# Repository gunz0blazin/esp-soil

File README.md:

# esp-soil

> **This is the `testing` branch.** It holds changes that are written but not yet running on the stakes or the dashboard server. `main` matches what's deployed right now. To see exactly what's new here, compare the branches: [`main...testing`](https://github.com/gunz0blazin/esp-soil/compare/main...testing). Once a change is flashed and checked on real hardware, it gets merged into `main` with a pull request.
>
> **In testing now**
> - **Deployment pipeline:** merging to `main` deploys the dashboard to the site's Raspberry Pi automatically (`ansible-pull` on a timer, with phone notifications). Firmware is flashed from the ESPHome add-on in Home Assistant, which pulls the shared firmware from `main`. The stakes are reached from home over Tailscale. Every push and pull request is checked on GitHub first. See [Deployment](#deployment) and [`deploy/README.md`](deploy/README.md).
> - **Shared firmware:** `firmware/common.yaml` is used by every stake; each stake has a small file with its number, IP and calibration (`firmware/stakes/`, plus a template for the Home Assistant add-on).
> - **Encryption:** the Home Assistant connection and every firmware update are encrypted with one key (`api_key`). Stakes no longer reboot when Home Assistant isn't connected.
> - **Board login:** the stake web page and `/metrics` require a username and password. Prometheus logs in using a password file. See [Board login](#board-login-testing).
> - **Dashboard stack:** stakes are listed in `dashboard/prometheus/targets/` (adding one needs no restart), image versions are pinned, the Grafana password comes from `.env`, and the dashboard is now called **Soil Monitor**.

Wi-Fi soil moisture stakes. Each stake is a small board with an ESP32-C3, a capacitive soil probe and an AHT10 temperature/humidity sensor in a 3D printed case. Push it into the soil like a plant marker and plug in a USB cable. It reports soil moisture, temperature, humidity and VPD over Wi-Fi to ESPHome / Home Assistant and Prometheus, and the included Grafana stack graphs it.

> **Status:** the breadboard version works and is graphing in Grafana. The stake PCB and snap-fit case are designed but haven't been built yet. The board is now a full KiCad project (`hardware/kicad/`) with the case in its 3D view. Run ERC/DRC there and plot Gerbers from it before ordering.

<!-- toc -->
**Contents**

- [What's in here](#whats-in-here)
- [The stake](#the-stake)
  - [Parts (per stake)](#parts-per-stake)
  - [Pins](#pins)
  - [Case](#case)
  - [Power](#power)
- [Setup](#setup)
- [Calibrating](#calibrating)
  - [Keeping readings honest](#keeping-readings-honest)
- [Data logging: Prometheus + Grafana](#data-logging-prometheus--grafana)
  - [What's in dashboard/](#whats-in-dashboard)
  - [Quick start](#quick-start)
  - [What a stake sends](#what-a-stake-sends)
  - [Prometheus](#prometheus)
  - [Grafana](#grafana)
  - [Viewing on a phone or remotely](#viewing-on-a-phone-or-remotely)
  - [Board login (testing)](#board-login-testing)
  - [Security notes](#security-notes)
  - [Maintenance](#maintenance)
  - [Troubleshooting](#troubleshooting)
- [Deployment](#deployment)
- [VPD](#vpd)
- [Testing on a breadboard](#testing-on-a-breadboard)
- [License](#license)
<!-- /toc -->

---

## What's in here

```
firmware/
  common.yaml              the stake firmware, shared by every stake
  stakes/                  one small file per stake: number, IP, calibration
  ha-stub.example.yaml     template for a stake in the Home Assistant ESPHome add-on
  moisture-test.yaml       breadboard test board: probe + AHT10 + OLED
  moisture-test-probe-only.yaml   same board, probe + OLED only
  legacy/                  the original 4-probe OLED + touch button build
hardware/
  kicad/                   KiCad project: schematic, PCB, 3D models + the case for fit checks
  pcb/                     v1 hand-made Gerbers, build guide PDF
  case/                    snap-fit case (3MF), OpenSCAD file, print notes
  legacy/                  case for the old 4-probe box
dashboard/                 Prometheus + Grafana in Docker, with the dashboard (see Data logging below)
deploy/                    automatic deploy to the site's Raspberry Pi (ansible-pull), setup and Tailscale guides
ci/, .github/workflows/    checks that run on GitHub for every push and pull request
secrets.example.yaml
```

---

## The stake

Each stake reads:

- Soil moisture %, calibrated to its own probe
- Raw probe voltage (for calibrating)
- Temperature and humidity
- Leaf VPD
- Wi-Fi signal

There's no screen. Everything goes to Grafana (see [Data logging](#data-logging-prometheus--grafana)), and there's a small web page on each stake at `http://<stake-ip>/` if you want a quick look.

### Parts (per stake)

| Part | Notes |
|---|---|
| Seeed XIAO ESP32-C3 | On 1x7 headers. Trim the pins under the board. Stick its FPC antenna to the inside of the lid |
| [DFRobot SEN0193](https://www.dfrobot.com/product-1385.html) capacitive soil probe | Cut off the JST plug, solder it straight to the board |
| AHT10 module | Check the pin order is VIN GND SCL SDA. Trim the header pins under the board |
| 10k + 33k resistors | Voltage divider, the C3's ADC tops out around 2.5 V |
| 0.1 µF ceramic cap | ADC noise filter |
| 100 µF electrolytic, 6.3 V+ | 5 mm across, 7 mm long max. Lay it flat |
| Stake PCB | 24 x 52 mm, 2 layers. KiCad project in `hardware/kicad/` |
| Printed case | `hardware/case/`, PETG |
| USB-C cable | Right-angle ones lie flat on the soil |

Everything is through-hole. Open `hardware/kicad/esp-soil-stake.kicad_pro` in KiCad 8+ for the schematic, the board and a 3D view with the case. [`hardware/kicad/README.md`](hardware/kicad/README.md) covers running the checks and making Gerbers. The assembly order is in `hardware/pcb/esp-soil-stake-build.pdf`. That PDF lists M2 screws, but the v2 case snaps together so you don't need them.

### Pins

| XIAO pin | Goes to |
|---|---|
| D1 / GPIO3 | Probe signal, through the 10k/33k divider |
| D4 / GPIO6 | AHT10 SDA |
| D5 / GPIO7 | AHT10 SCL |
| 3V3 / GND | AHT10 and probe power |

### Case

Two parts, snaps together, no screws. Both print without supports. The probe sticks out the bottom through a slot you seal with silicone, and USB-C comes out the top. Print notes and tuning are in [`hardware/case/PRINT-NOTES.md`](hardware/case/PRINT-NOTES.md).

### Power

It runs off USB, about 0.3 W per stake. A multi-port USB charger with a cable to each stake works well. Power banks aren't practical for long-term monitoring: 100 days would take 150,000+ mAh, and many power banks shut off at a draw this low anyway.

---

## Setup

You need [ESPHome](https://esphome.io/) 2026.9 or newer, either the Home Assistant add-on or standalone. The firmware is split in two:

- **`firmware/common.yaml`**: everything the stakes share. You don't flash it directly.
- **One small file per stake**: its number, static IP and calibration, plus your secrets. It pulls in `common.yaml`.

**With the Home Assistant ESPHome add-on** (how the stakes are meant to be managed):

1. Add your secrets to the add-on's **Secrets** (values in [`secrets.example.yaml`](secrets.example.yaml)): Wi-Fi, `web_username` / `web_password`, and `api_key`.
2. Create one device per stake and paste [`firmware/ha-stub.example.yaml`](firmware/ha-stub.example.yaml) into it. Change the values at the top:
   ```yaml
   substitutions:
     plant: "1"            # stake number, used in the sensor names
     node_name: soil-stake-1
     stake_ip: 10.42.0.11  # the stake's static IP (it sets this on itself)
     dry_v: "1.92"         # calibration, see below
     wet_v: "0.92"
   ```
   The stub fetches `common.yaml` from the `main` branch on GitHub every time it builds, so the add-on always flashes the merged firmware.
3. Flash over USB the first time (**Install → Plug into this computer**; browser flashing needs Chrome or Edge). After that it updates over Wi-Fi.
4. Nothing to set on the router: each stake gives itself its `stake_ip` (static) as soon as it joins the Wi-Fi. The network's gateway and subnet mask are set once in `common.yaml` (defaults `10.42.0.1` / `255.255.255.0`); a stake on a different network, like a test probe at home, overrides them in its own file.

**Standalone, from this repo:** copy `secrets.example.yaml` to `firmware/stakes/secrets.yaml`, edit `firmware/stakes/soil-stake-N.yaml`, and run `esphome run firmware/stakes/soil-stake-1.yaml`.

**Keep `api_key` safe** (a password manager). It encrypts both the Home Assistant connection and every firmware update, and a stake flashed with it can only be updated over Wi-Fi with the same key.

The full site setup (Pi, Tailscale, Home Assistant) is in [`deploy/README.md`](deploy/README.md).

---

## Calibrating

Out of the box the % means nothing. Every probe reads a little different, so each stake gets its own dry and wet value.

The probe voltage goes **down** as the soil gets wetter. On the stake you're reading it after the divider, so expect roughly 1.9 V dry and 0.9 V soaked.

1. Watch the stake's **raw** sensor (`Plant N raw`) in Grafana, the stake's web page, or the logs.
2. **Dry:** probe in the air or bone-dry mix. That's `dry_v`.
3. **Wet:** in the soil, watered until it drains, 30 minutes later. That's `wet_v`.
4. Put both in the stake's file (`dry_v` / `wet_v`) and reflash.

0% means "as dry as the dry reference" and 100% means "right after a full watering." It's not actual water content, just a consistent scale.

### Keeping readings honest

- Same depth for every stake, and don't move a stake once it's calibrated. Moving it changes the reading.
- Press the soil firmly around the probe so there's no air gap.
- Only the probe below its line goes in the soil. The case keeps the electronics above it.
- Fertilizer salts slowly push readings up. If the numbers creep up for no reason, redo the wet value.
- The AHT10 sits right at soil level, so it reads warmer and more humid than the air higher up. The ESP also warms the board a bit. Compare against a thermometer you trust once and set the offset in the YAML.

---

## Data logging: Prometheus + Grafana

The stakes don't store any history themselves. A small Docker Compose stack in `dashboard/` does that:

- **Prometheus** visits every stake every 15 seconds, logs in, reads its current values from `http://<stake>/metrics`, and keeps them in a time-series database for 2 years.
- **Grafana** reads from Prometheus and draws the dashboard: current values at the top, history graphs below.

Prometheus *pulls* from the stakes. A stake never sends data anywhere on its own, so if Prometheus is down, readings from that time just aren't recorded (the stakes keep running normally). Home Assistant is a separate path: it talks to each stake over the ESPHome native API and doesn't need Prometheus at all.

### What's in `dashboard/`

| File | What it does |
|---|---|
| `docker-compose.yml` | Runs Prometheus (port 9090) and Grafana (port 3000) at pinned versions, with a named volume for each so data survives restarts and image updates |
| `prometheus/prometheus.yml` | Scrape settings and the board login |
| `prometheus/targets/stakes.yml` | The list of stakes to read. Prometheus re-reads it on its own |
| `prometheus/esp_web_password` | The board password Prometheus logs in with. You create it on the server; it's gitignored. `esp_web_password.example` shows the format |
| `grafana/provisioning/datasources/prometheus.yml` | Connects Grafana to Prometheus automatically (no clicking through the UI) |
| `grafana/provisioning/dashboards/dashboards.yml` | Tells Grafana to load every dashboard JSON in `grafana/dashboards/` |
| `grafana/dashboards/*.json` | The dashboard itself |
| `SETUP.md` | Step-by-step install, phone access and adding stakes |

### Quick start

On the site's Raspberry Pi this is all automatic: see [Deployment](#deployment). To run the stack by hand on any Linux machine with Docker:

```bash
cd dashboard
nano prometheus/targets/stakes.yml                                # one entry per stake, see below
printf '%s' 'your-long-password' > prometheus/esp_web_password    # same as web_password on the stakes
chmod 644 prometheus/esp_web_password
echo 'GRAFANA_ADMIN_PASSWORD=pick-one' > .env                     # used the first time Grafana starts
docker compose up -d
```

- Grafana: `http://<server-ip>:3000`, user `admin`. The dashboard opens as the home page.
- Prometheus: `http://<server-ip>:9090`. Check **Status → Target health** first: every stake should say **UP**.

Any Linux machine, VM or container host on the same network as the stakes works. The whole stack is light: a few hundred MB of RAM, and storage is small (see [Storage and retention](#storage-and-retention)).

---

### What a stake sends

With `web_server:` and `prometheus:` in the firmware, each stake serves its sensor values as plain text at `/metrics`, behind the board login. You can open it in a browser (it asks for the username and password) or `curl` it with `-u`:

```text
$ curl -u esp:your-long-password http://192.168.1.XXX/metrics
#TYPE esphome_sensor_value gauge
#TYPE esphome_sensor_failed gauge
esphome_sensor_value{id="probe_raw",name="Plant 1 raw",unit="V"} 1.455
esphome_sensor_failed{id="probe_raw",name="Plant 1 raw"} 0
esphome_sensor_value{id="moisture",name="Plant 1 moisture",unit="%"} 46
esphome_sensor_failed{id="moisture",name="Plant 1 moisture"} 0
...
```

Every sensor becomes one `esphome_sensor_value` line. The `name` label is the sensor's name from the YAML, and that's what the dashboard and the queries below match on. `esphome_sensor_failed` is `1` when a sensor has no valid reading (for example the AHT10 isn't responding). The exact set of labels can vary a little between ESPHome versions.

| Sensor (`name`) | Unit | How often the stake updates it |
|---|---|---|
| `Plant N raw` | V | every 10 s (median of the last 7 samples, sampled every 5 s) |
| `Plant N moisture` | % | every 10 s (calculated from the raw value) |
| `Plant N temperature` | °C | every 15 s |
| `Plant N humidity` | % | every 15 s |
| `Plant N leaf VPD` | kPa | every 15 s |
| `Plant N WiFi` | dBm | every 60 s |

`N` is the `plant` value in each stake's file. Prometheus scrapes every 15 s and records whatever the latest value is at that moment.

---

### Prometheus

#### Configuration

`dashboard/prometheus/prometheus.yml`:

```yaml
global:
  scrape_interval: 15s          # how often every stake is read

scrape_configs:
  - job_name: esphome
    metrics_path: /metrics
    basic_auth:                 # the board login, sent on every scrape
      username: esp             # must match web_username on the stakes
      password_file: /etc/prometheus/esp_web_password
    file_sd_configs:            # the list of stakes, in its own file
      - files:
          - /etc/prometheus/targets/*.yml
        refresh_interval: 1m
```

`dashboard/prometheus/targets/stakes.yml`:

```yaml
- targets: ["10.42.0.11:80"]      # the stake's static IP and web_server port
  labels: {board: soil-stake-1}   # extra label so you can tell stakes apart
- targets: ["10.42.0.12:80"]
  labels: {board: soil-stake-2}
```

- **`basic_auth`** applies to every stake in the job, so all stakes share one username and password. Stakes still on firmware without a login just ignore it.
- **One entry per stake** in `targets/stakes.yml`. The `board` label is added to every value from that stake, which makes queries and graphs easier to read.
- **Adding or removing a stake needs no restart:** Prometheus re-reads the targets file within a minute.
- **Each stake's IP here must match `stake_ip` in its firmware file.** The GitHub checks compare the two and fail if they don't.
- **After editing `prometheus.yml` itself**, apply it with `docker compose restart prometheus`. A restart doesn't lose any data. (The Pi's deploy does this for you, and only when that file changed.)

Prometheus also adds two labels on its own: `job="esphome"` and `instance="<ip>:80"`. It also records a few series per stake about the scrape itself, the most useful being `up`, which is `1` when the last read worked and `0` when it didn't.

#### Checking the stakes are being read

Open `http://<server-ip>:9090/targets` (**Status → Target health**). Every stake should be **UP**, with a recent "Last scrape" time.

If a stake shows **DOWN**, the error under it says why. In the screenshot (sample data), stake 3 has a different password from the one Prometheus is sending, so it's rejected with **401 Unauthorized** while the other two log in fine. The usual causes are in [Troubleshooting](#troubleshooting).

#### Querying

The **Query** page runs PromQL and can graph the result. This is useful for one-off questions the dashboard doesn't answer, and for testing a query before you put it in a Grafana panel.

*Sample data: three stakes over three days. Each sharp rise is a watering, followed by a slow dry-down.*

Queries that are handy for this project (all tested):

| What you want | PromQL |
|---|---|
| Current moisture, every stake | `esphome_sensor_value{name=~".*moisture"}` |
| Driest reading in the last 24 h | `min_over_time(esphome_sensor_value{name=~".*moisture"}[24h])` |
| Dry-down rate in % per hour (negative = drying) | `deriv(esphome_sensor_value{name=~".*moisture"}[1h]) * 3600` |
| Rough hours until a stake reaches 40% | `(esphome_sensor_value{name=~".*moisture"} - 40) / -(deriv(esphome_sensor_value{name=~".*moisture"}[3h]) * 3600) > 0` |
| Stakes that aren't responding | `up{job="esphome"} == 0` |
| Average temperature over the last day (°C) | `avg_over_time(esphome_sensor_value{name=~".*temperature"}[1d])` |
| Wi-Fi signal per stake | `esphome_sensor_value{name=~".*WiFi"}` |
| How many sensors each stake reports | `count by (board) (esphome_sensor_value)` |

The "hours until 40%" estimate only returns a value for stakes that are currently drying and are still above 40%. It's a straight-line projection from the last 3 hours, so treat it as a rough guide.

#### Storage and retention

- History is kept for **2 years** (`--storage.tsdb.retention.time=2y` in `docker-compose.yml`). Older data is deleted automatically.
- Data lives in the `prometheus-data` Docker volume, so it survives `docker compose restart`, `down`/`up` and image updates.
- Each stake produces about a dozen series at one sample every 15 s. Prometheus compresses this well, so two years for one stake comes to well under 100 MB.

---

### Grafana

#### Provisioning (set up from files)

Grafana is configured entirely from files in `dashboard/grafana/`, so a fresh install comes up ready to use:

- **Data source:** `provisioning/datasources/prometheus.yml` adds Prometheus at `http://prometheus:9090` (the container name on the Compose network) and makes it the default.
- **Dashboard:** `provisioning/dashboards/dashboards.yml` loads every JSON file in `grafana/dashboards/`. `docker-compose.yml` sets the bundled dashboard as Grafana's home page.
- **Other settings** (in `docker-compose.yml`): dark theme by default, and embedding is allowed so the dashboard can be shown inside a Home Assistant **Webpage** card.

UI edits to the dashboard are allowed and get saved in Grafana's own database. To keep a change for good (and in git), export it as JSON (**Export → Export as JSON**) and replace the file in `grafana/dashboards/`.

#### The dashboard

*Preview drawn from the dashboard file with sample data for three stakes. Panel layout, queries, units and color thresholds match the JSON; Grafana's own styling differs slightly.*

The default view is the last 24 hours, refreshing every 30 seconds.

**Right now** — stat tiles with the latest value, colored by threshold, and a sparkline of the time range:

| Panel | Shows | Colors |
|---|---|---|
| Soil moisture | Every `…moisture` sensor, one tile per stake | red under 30%, orange 30–45%, green 45–85%, blue 85%+ |
| Temperature | Every `…temperature` sensor, converted to °F | blue under 70, green 70–85, orange 85–90, red 90+ °F |
| Humidity | Every `…humidity` sensor | orange under 40%, green 40–70%, blue 70%+ |
| Leaf VPD | Every `…leaf…vpd` sensor | blue under 0.4, light green 0.4–0.8, green 0.8–1.2, purple 1.2–1.6, red 1.6+ kPa |
| Probe voltage | Every `…raw` sensor | none (for calibration) |

**Soil**

- **Soil moisture**: history for every stake, 0–100%, with a dashed line and red shading below 40%.
- **Probe raw voltage (calibration)**: the voltage behind each moisture reading. Use it to pick `dry_v` and `wet_v` (see [Calibrating](#calibrating)).

**Climate**

- **Temperature** (°F) with the 70–85 °F band shaded.
- **Humidity** (%).
- **VPD** (kPa) with the same color bands as the Leaf VPD tile.

#### How new stakes show up

The panels don't list stakes one by one. Each query matches sensor *names* with a case-insensitive pattern, for example:

```promql
esphome_sensor_value{name=~"(?i).*moisture.*"}
```

So as soon as Prometheus is reading a new stake, its moisture, temperature, humidity, VPD and raw voltage appear on the dashboard with no Grafana changes. This also means a sensor needs one of those words in its name to be picked up.

Every tile and graph line is labelled by stake (**Plant 1**, **Plant 2**, …), taken from the sensor name. Each query wraps the match in `label_replace` to build that label:

```promql
label_replace(label_replace(esphome_sensor_value{name=~"(?i).*moisture.*"},
  "stake", "$1", "name", "(.*)"),                 # default: the full sensor name
  "stake", "Plant $1", "name", "Plant ([0-9]+) .*")  # stake firmware: "Plant N"
```

The panels use `{{stake}}` as their legend. A sensor whose name doesn't start with `Plant N` still shows up, under its full name.

#### Known limitations

- **Leaf VPD tile vs VPD graph:** the tile matches `leaf…vpd`, the graph matches any sensor with `vpd` in its name. With the stake firmware they show the same sensors.
- Short gaps (a stake rebooting, a missed scrape) are bridged on the graphs if they're under 5 minutes. Longer gaps show as breaks.

---

### Viewing on a phone or remotely

- **On your home network:** open `http://<server-ip>:3000` and use "Add to Home Screen". Panels stack into one column on a narrow screen.
- **Away from the site:** over Tailscale, at `http://<pi-tailscale-name>:3000` (set up in [`deploy/README.md`](deploy/README.md#2-tailscale-reach-the-site-from-home)). Don't open ports 3000 or 9090 to the internet.
- **Inside Home Assistant:** add a **Webpage** card or dashboard pointing at `http://<server-ip>:3000/d/soil-monitor?kiosk`. `?kiosk` hides Grafana's menus.

More detail is in [`dashboard/SETUP.md`](dashboard/SETUP.md).

### Board login (testing)

Each stake's web page and `/metrics` sit behind one username and password, set in ESPHome's `secrets.yaml`:

```yaml
# secrets.yaml (next to the firmware, gitignored)
web_username: "esp"
web_password: "your-long-password"
```

```yaml
# firmware/common.yaml (the values come from each stake file's secrets)
web_server:
  port: 80
  auth:
    username: ${web_username}
    password: ${web_password}
    type: basic
```

**How it works**

- The login covers everything the web server serves: the live web page *and* `/metrics`. That's why Prometheus has to log in too.
- Prometheus sends the username from `prometheus.yml` and reads the password from `prometheus/esp_web_password`, which `docker-compose.yml` mounts into the container. The password never goes in git.
- Every stake uses the same login, because one scrape job sends one set of credentials.
- **`type: basic` is required.** Prometheus only does basic auth. ESPHome currently defaults to basic, but the default switches to digest in ESPHome 2027.1, so the firmware sets it explicitly.

**Rolling it out** (order matters)

1. Add `web_username` / `web_password` to ESPHome's `secrets.yaml`.
2. On the server, put the same password in `prometheus/esp_web_password`. On the Pi that's `/etc/esp-soil/esp_web_password`, and the deploy copies it in. By hand: `chmod 644` it and run `docker compose up -d --force-recreate prometheus`. Create the file *before* the container starts: if it's missing, Docker creates a folder with that name and every scrape fails.
3. OTA the stakes one at a time. Boards without a login ignore the credentials, so nothing breaks while some stakes are updated and some aren't.
4. Check `http://<server-ip>:9090/targets`: every stake should be **UP**.

**Checking a stake by hand**

```bash
curl -s -o /dev/null -w '%{http_code}\n' http://<stake-ip>/metrics        # 401 = login is on
curl -s -u esp:your-long-password http://<stake-ip>/metrics | head     # readings come back
```

**Changing the password:** update `web_password` and OTA every stake, then update `prometheus/esp_web_password` and restart Prometheus. Stakes show **401** in between, so do it in one sitting.

### Security notes

- **The stakes have a login,** but it's HTTP basic auth over plain HTTP. The password is only base64-encoded, so anyone who can capture traffic on your network could read it. It stops casual access to the web page and readings; keep the stakes on a network you trust (a separate VLAN for IoT devices is a good idea).
- **Use a password that isn't used anywhere else,** since it's stored in plain text in `secrets.yaml` and `esp_web_password`.
- **The Grafana admin password** comes from `GRAFANA_ADMIN_PASSWORD` in `dashboard/.env` (on the Pi, from `/etc/esp-soil/grafana_admin_password`). It's only applied the first time Grafana starts; after that, change it in Grafana.
- **Prometheus (9090) has no login.** Keep it on your local network.

### Maintenance

| Task | How |
|---|---|
| Add a stake | Flash it with the same secrets, and add an entry to `prometheus/targets/stakes.yml`. No restart needed. Full steps: [`deploy/README.md`](deploy/README.md#adding-a-stake) |
| Change the board password | See [Board login](#board-login-testing) |
| Remove a stake | Delete its block and restart Prometheus. Its old history stays until it ages out |
| Update Prometheus and Grafana | Change the pinned version in `docker-compose.yml` on `testing`. The checks confirm the new tag exists with an ARM64 build; after the merge, the Pi pulls it |
| Back up the history | Stop Prometheus (`docker compose stop prometheus`), copy the `prometheus-data` volume (named `esp-soil_prometheus-data` on the Pi, `dashboard_prometheus-data` if you started it by hand from `dashboard/`), then start it again |
| Reset Grafana settings | Remove the `grafana-data` volume. The data source and dashboard come back from the provisioning files on the next start |

Don't run `docker compose down -v` unless you mean it: `-v` deletes both volumes, including all history.

### Troubleshooting

| Symptom | Likely cause | Fix |
|---|---|---|
| Target **DOWN**, "connection refused" or timeout | Stake is off, on a different IP, or not on Wi-Fi | Check the stake's IP in your router and open `http://<ip>/metrics` from the server |
| Target **DOWN**, "401 Unauthorized" | The stake's password or username doesn't match what Prometheus sends | Compare `web_username` / `web_password` with `prometheus.yml` and `esp_web_password` (no trailing newline; `printf '%s'` avoids one) |
| Every target **DOWN** with an error about the password file | `esp_web_password` didn't exist when the container started, so Docker made a folder | `docker compose down`, delete the folder, create the file, `docker compose up -d` |
| Browser asks for a login on the stake's page | Expected on this branch | Use `web_username` / `web_password` |
| Target **DOWN**, "404 Not Found" | Firmware is missing `prometheus:` | Add `web_server:` and `prometheus:` to the YAML and reflash |
| Target **UP** but the stake isn't on the dashboard | Sensor names don't contain `moisture`, `temperature`, `humidity`, `vpd` or `raw` | Check the names at `/metrics` |
| Whole dashboard says "No data" | Grafana can't reach Prometheus | Both containers must be in the same Compose stack; check **Connections → Data sources → Prometheus → Test** |
| History is gone after a restart | A volume was removed | Use `restart` or `down`/`up`, not `down -v` |
| Graph times look shifted | Grafana uses the browser's time zone | Change it in the dashboard settings or your Grafana profile |

---

## Deployment

The stakes and a Raspberry Pi live at a site that can be off your home network. The Pi runs Prometheus and Grafana; Home Assistant at home manages the stakes' firmware over Tailscale.

| What changed on `main` | What happens |
|---|---|
| `dashboard/` (Prometheus, Grafana, the list of stakes) | **Automatic.** The Pi checks GitHub every 5 minutes. On a new commit it validates the config, deploys it, restarts only what changed, checks everything is healthy, and sends a phone notification with how many stakes it can reach. A bad config is rejected before anything live changes |
| `firmware/` | **You choose when.** Each stake's file in the ESPHome add-on pulls `firmware/common.yaml` from `main`. Flash one stake, check it, then the rest |
| `deploy/` | The Pi updates its own deploy command and timer |

**How work flows**

1. Make changes on `testing` and push. GitHub runs the checks (below) on every push.
2. Open a pull request into `main`. Merge when the checks are green.
3. The Pi deploys dashboard changes on its own; firmware gets flashed from the add-on.
4. Fast-forward `testing` to `main`, so `testing` only ever shows new, unmerged work.

**Checks on every push and pull request** (`.github/workflows/checks.yml`, on GitHub's runners with throwaway secrets, so it's safe on a public repo):

- every stake file and the Home Assistant stub validate with the pinned ESPHome version, and the firmware compiles
- `promtool` accepts the Prometheus config; the compose file and the list of stakes are valid; the pinned images exist with ARM64 builds for the Pi
- the deploy playbook runs end to end on the runner, a second run changes nothing, Grafana loads the dashboard and Prometheus finds every stake

**Why the Pi pulls instead of GitHub pushing:** nothing on the internet can make the Pi run code. It only ever pulls `main`, and only you can merge to `main`. No ports are opened at the site.

**First deployment, in order:** [Going live, step by step](deploy/README.md#going-live-step-by-step).

**Setting it up** (Pi bootstrap, secrets, notifications, the ESPHome add-on, day-to-day steps, rollbacks and troubleshooting): [`deploy/README.md`](deploy/README.md). Remote access to the site: [`deploy/TAILSCALE.md`](deploy/TAILSCALE.md).

---

## VPD

Leaf VPD (vapor pressure deficit) is calculated from the AHT10's temperature and humidity. It assumes the leaf surface is slightly cooler than the air; the offset is `leaf_offset_c` in the YAML, default 2 °C.

---

## Testing on a breadboard

`firmware/moisture-test.yaml` is the pre-PCB test build: an ESP32 DevKit with one probe, an AHT10 and a 0.96" OLED showing moisture, temp, RH and VPD.

| Part | ESP32 pin |
|---|---|
| Probe signal | GPIO32 |
| OLED SDA / SCL | GPIO21 / GPIO22 |
| AHT10 SDA / SCL | GPIO25 / GPIO26 |

Lessons from the breadboard build:

- **Keep probes on ADC1 pins (GPIO32–35).** ADC2 stops working when Wi-Fi is on.
- **Give the AHT10 its own I2C bus.** It can lock up a shared bus and take the OLED down with it.
- **Check your OLED's pin order.** Some are GND-VCC-SCL-SDA and some are VCC-GND-SCL-SDA.
- **Cheap probes:** look at the chip. You want **TLC555**, not **NE555**. The NE555 ones don't behave at 3.3 V.
- **No probes yet?** A 10k potentiometer works: outer legs to 3V3 and GND, middle leg to the probe pin. Turn it and watch the % move.

The original 4-probe box with touch buttons is still in `firmware/legacy/` and `hardware/legacy/` if anyone wants a single-box version.

---

## License

See [`LICENSE`](LICENSE).

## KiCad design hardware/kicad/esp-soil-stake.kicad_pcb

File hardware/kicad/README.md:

# Stake PCB: KiCad project

The full stake board as a KiCad project: schematic, PCB, footprints, 3D models for every part, and the snap-fit case loaded into the 3D viewer, so you can check the fit before ordering anything.

<!-- toc -->
**Contents**

- [Opening it](#opening-it)
- [Running the checks in KiCad](#running-the-checks-in-kicad)
- [Gerbers](#gerbers)
- [Parts](#parts)
- [Reading the board](#reading-the-board)
- [What's been checked](#whats-been-checked)
- [Measure these before ordering](#measure-these-before-ordering)
- [Regenerating](#regenerating)
- [Credits](#credits)
<!-- /toc -->

## Opening it

1. Install KiCad 8 or newer (kicad.org). It's saved in KiCad 8 format, so 8, 9 and 10 all open it.
2. Open `esp-soil-stake.kicad_pro`.
3. Everything is self-contained. The symbols, footprints and 3D models live in this folder (`esp-soil.kicad_sym`, `esp-soil.pretty/`, `3d/`) and are hooked up through the project's own library tables. Nothing needs installing.

## Running the checks in KiCad

**Schematic (ERC):** open the schematic, then **Inspect → Electrical Rules Checker → Run ERC**. You should get 0 errors. Unused XIAO pins have no-connect flags, and GND has a PWR_FLAG.

**PCB (DRC):** open the PCB, then **Inspect → Design Rules Checker**. Leave **Refill all zones** ticked and turn on **Test for parity between PCB and schematic**, then **Run DRC**.

- The GND pour on the back isn't pre-filled. DRC fills it, or press **B** in the PCB editor.
- The rules are set for a cheap 2-layer fab (JLCPCB/PCBWay): 0.2 mm clearance, 0.3 mm copper to edge. You can see them under **File → Board Setup → Design Rules**.
- KiCad may warn that the XIAO's courtyard goes past the board edge. That's on purpose: the USB-C port overhangs by 1.4 mm so the cable reaches it through the case's top opening.

**3D fit with the case:** in the PCB editor, **View → 3D Viewer** (Alt+3). The case is a 3D-only part called `CASE1`. The back shell is solid and the lid is see-through, so you can look inside.

- To hide part of the case: in the PCB editor, hover over the `CASE OUTLINE` box on the F.Fab layer and press **E** to open CASE1's properties. On the **3D Models** tab, untick **Show** for the shell or the lid.

## Gerbers

**Ready-made:** `gerbers/esp-soil-stake-v1.1-gerbers.zip` is plotted straight from this board file by `source/gen_gerbers.py`. It has both copper layers with the back GND pour filled, both masks, both silkscreens, the outline, and PTH + NPTH drill files. It was cross-checked by reading it back with [gerbonara](https://github.com/jaseg/gerbonara), a separate Gerber parser. `gerbers/preview-v1.1.png` shows what the fab will see. Upload the zip as-is.

**From KiCad**, if you change the board: once ERC and DRC are clean, **File → Fabrication Outputs → Gerbers (.gbr)**, then **Generate Drill Files** in the same dialog. Zip the folder and upload it to the fab.

The hand-made Gerbers in `../pcb/` are the v1 board. This project is v1.1 and is the one to order from now on. The routing is the same; the differences are:

- The resistors and C1 use KiCad's stock footprints (slightly smaller pads, and C1's legs are 2.5 mm apart).
- The board text moved to the back silkscreen.

## Parts

| Ref | Part | Footprint | Notes |
|---|---|---|---|
| U1 | Seeed XIAO ESP32-C3 | `XIAO_ESP32C3_THT` | On 1x7 male headers. Pin map and spacing come from Seeed's own KiCad library. **Plug in the FPC antenna that comes with it.** The C3 has no antenna on the board. |
| J1 | AHT10 breakout (VIN GND SCL SDA) | `AHT10_Module_1x04_P2.54mm` | On its own 4-pin header |
| P1 | DFRobot SEN0193, 98 x 23 mm | `SEN0193_Wire_Pads_1x03_P2.54mm` | Cut the JST plug off, solder the leads: A = signal, + = 3V3, − = GND |
| R1 | 10k, 1/4 W (small, DIN0204) | KiCad `R_Axial_DIN0204..._Vertical` | Stands up |
| R2 | 33k, 1/4 W (small, DIN0204) | same | Stands up |
| C1 | 100 nF ceramic disc | KiCad `C_Disc_D3.0mm_W1.6mm_P2.50mm` | |
| C2 | 100 µF 6.3 V+ electrolytic, **5 mm across, 7 mm long max** | `CP_Radial_D5.0mm_P2.50mm_LaidFlat_L7mm` | Bend it flat toward the AHT10 |
| H1, H2 | 2.2 mm holes | `MountingHole_2.2mm_M2` | The case's locating pins go through these |
| CASE1 | Case v2 | 3D-only | Not a real part. It's excluded from the BOM and position files. |

## Reading the board

- **Probe pads (P1, A + −)** along the bottom edge are where the probe's cable gets soldered after you cut its JST plug off:
  - **A** takes the blue signal wire. It runs through R1/R2 to D1/GPIO3.
  - **+** takes the red wire (3.3 V).
  - **−** takes the black wire (GND).
  - Check the wire colors against your probe's own labels before soldering, and keep the leads about 3 mm long.
- **C2** sits in the outlined box above the probe pads on the right. It's a reserve on the 3.3 V line that covers the XIAO's Wi-Fi current bursts. **It has to go in the right way round:** long leg in the square **+** pad, striped side in the round pad. Bend it flat into the box.
- **There are no ground traces.** The whole back layer is a GND copper pour, and every GND pad joins it through four small spokes. In KiCad, press **B** to fill it and the GND ratsnest lines go away.

## What's been checked

`source/verify_kicad.py` checks the project independently, without KiCad: **33 checks pass, 0 fail.** The full output is in `source/verify-report.txt`.

- **Files:** every file parses as valid KiCad syntax. The board, schematic, symbols and footprints all load in [kiutils](https://github.com/mvnmgrx/kiutils), a separate KiCad file parser.
- **Schematic:** connections are rebuilt from the actual pin and wire positions. No dangling wires, and every pin is either connected or flagged no-connect. Power nets are driven.
- **Schematic vs. board:** every pad's net matches the schematic, and footprints and symbols match one-to-one.
- **Board:**
  - Every net is fully routed. GND runs through the back pour.
  - Clearances: the smallest pad-to-pad gap is 0.37 mm and the smallest track-to-pad gap is 0.97 mm. Rings and edge clearance are all inside the rules.
  - No courtyard overlaps.
- **Fit in the real case geometry**, at 0.2 mm resolution:
  - No part touches the case.
  - The board rests on its ledges and posts. The lid bosses clamp it, and the only case material passing through the board is the two pins in H1/H2.
  - A full-size USB-C plug reaches the port.
  - The probe clears its slot.
  - There's about 21 x 27 mm of room on the lid's underside over the probe for the antenna.

The checker also gives two build notes:

- **Trim the header pins under the board.** Standard male headers stick out about 4.4 mm under the PCB, and the case only allows about 2.7 mm. Snip them after soldering, the same as the resistor leads.
- **Stick the XIAO's FPC antenna** to the underside of the lid over the probe end, away from the AHT10 vents.

## Measure these before ordering

These sizes came from datasheets and listings, not from your parts:

- **AHT10 module:** modeled as 16.1 x 11.2 mm with the header along the long edge. Breakouts vary. If yours is bigger, check it clears the lid boss beside H2: there's about 1.3 mm of room past the module's far edge.
- **C2:** 100 µF caps come in 5 x 7, 5 x 11 and 6.3 x 5 mm. Laid flat, there's room for a body up to about 7.5 mm long.
- **XIAO:** modeled at 21 x 17.8 mm with a 1.2 mm PCB, sitting on a 2.5 mm header spacer.

## Regenerating

Everything here is generated, so change the generator rather than editing the files by hand. If you do edit in KiCad, that's fine; just don't rerun the generator afterward or it will overwrite your changes.

```bash
cd source
python3 gen_kicad.py      # rewrites the project + 3D models (reads ../../case/source/gen_case.py for the case)
python3 verify_kicad.py   # all the checks above, exit code 1 on failure
python3 render_3d.py      # render-3d.png
python3 gen_gerbers.py    # ../gerbers/ fab files + zip
```

They need numpy, scikit-image and matplotlib; `pip install kiutils` for the extra parser check.

## Credits

- The XIAO pin map and spacing come from [Seeed Studio's OPL KiCad library](https://github.com/Seeed-Studio/OPL_Kicad_Library).
- The resistor and C1 footprints and 3D models are KiCad's stock libraries ([kicad-footprints](https://github.com/KiCad/kicad-footprints), [kicad-packages3D](https://github.com/KiCad/kicad-packages3D)), CC-BY-SA 4.0 with KiCad's library exception.
- The XIAO, AHT10, probe and C2 models are simple block models made for the fit check, not detailed parts.

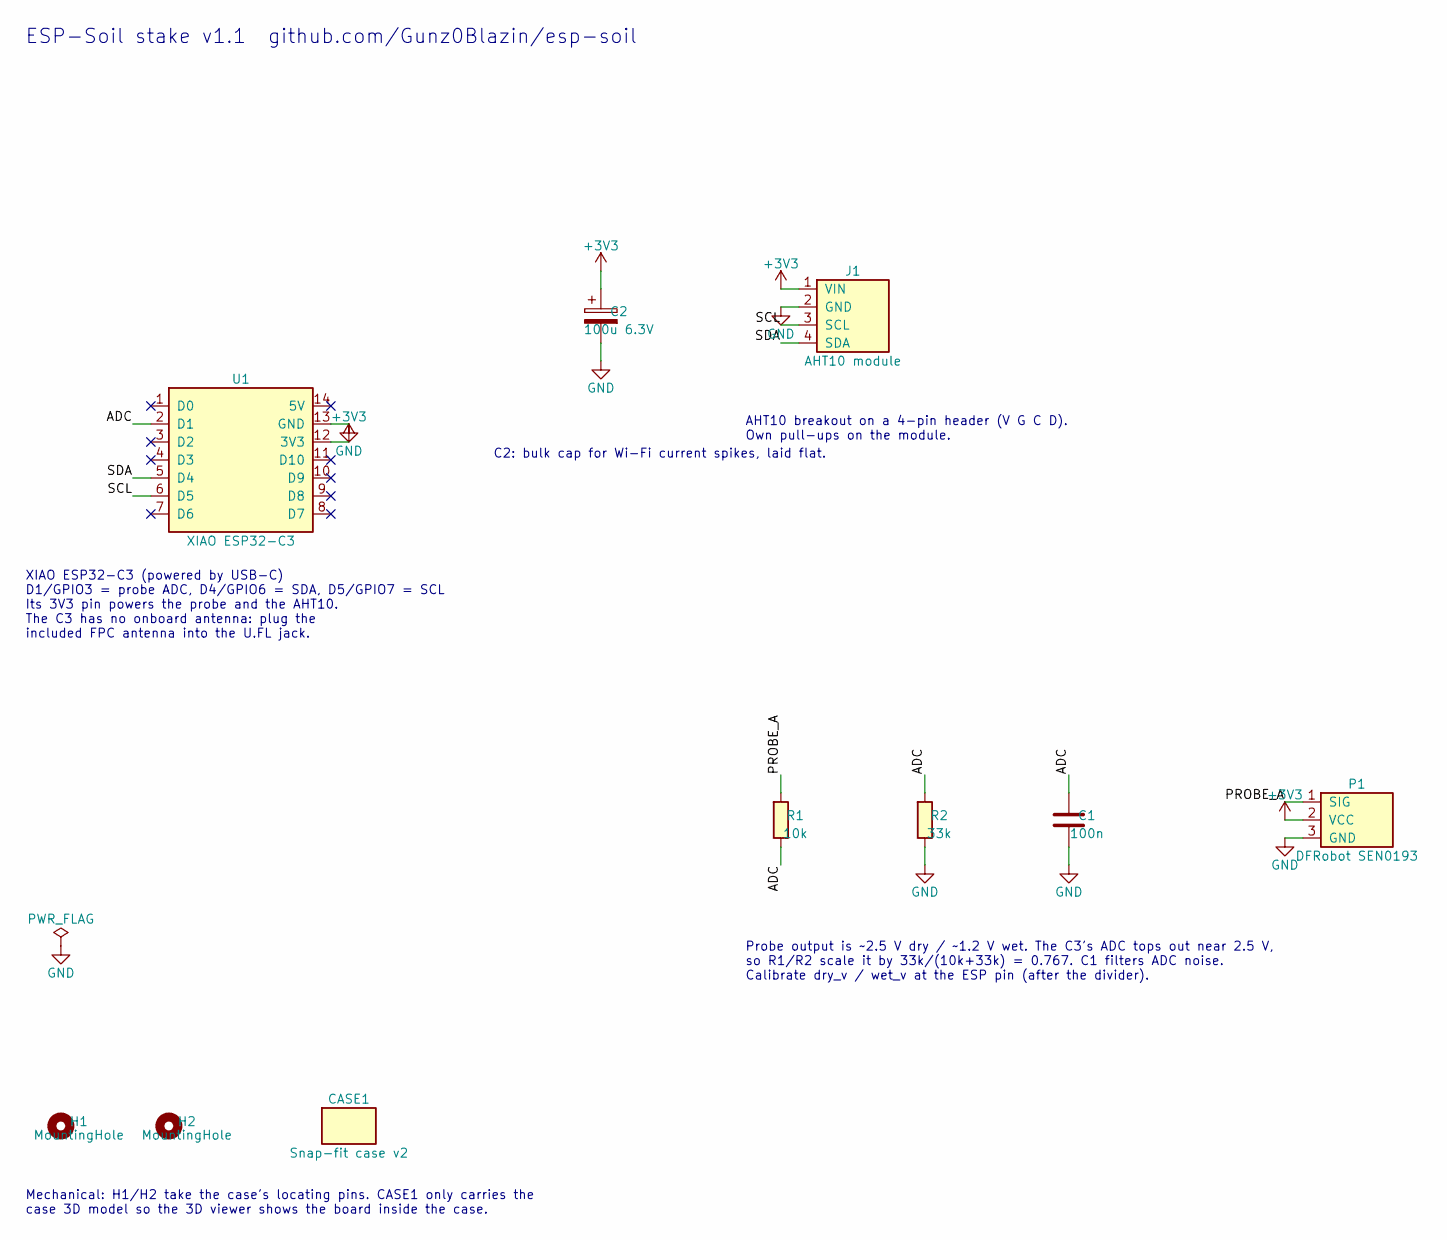
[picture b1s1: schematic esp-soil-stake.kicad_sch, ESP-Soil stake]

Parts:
C1: 100n; C_Disc_D3.0mm_W1.6mm_P2.50mm
C2: 100u 6.3V; CP_Radial_D5.0mm_P2.50mm_LaidFlat_L7mm
CASE1: Snap-fit case v2; ESP-Soil_Stake_Case_v2
H1, H2: MountingHole; MountingHole_2.2mm_M2
J1: AHT10 module; AHT10_Module_1x04_P2.54mm
P1: DFRobot SEN0193; SEN0193_Wire_Pads_1x03_P2.54mm
R1: 10k; R_Axial_DIN0204_L3.6mm_D1.6mm_P2.54mm_Vertical
R2: 33k; R_Axial_DIN0204_L3.6mm_D1.6mm_P2.54mm_Vertical
U1: XIAO ESP32-C3; XIAO_ESP32C3_THT

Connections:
+3V3: C2.1, J1.1 (VIN), P1.2 (VCC), U1.12 (3V3)
/ADC: C1.1, R1.2, R2.1, U1.2 (D1)
/PROBE_A: P1.1 (SIG), R1.1
/SCL: J1.3 (SCL), U1.6 (D5)
/SDA: J1.4 (SDA), U1.5 (D4)
GND: C1.2, C2.2, J1.2 (GND), P1.3 (GND), R2.2, U1.13 (GND)

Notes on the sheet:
XIAO ESP32-C3 (powered by USB-C) D1/GPIO3 = probe ADC, D4/GPIO6 = SDA, D5/GPIO7 = SCL Its 3V3 pin powers the probe and the AHT10. The C3 has no onboard antenna: plug the included FPC antenna into the U.FL jack.
AHT10 breakout on a 4-pin header (V G C D). Own pull-ups on the module.
Probe output is ~2.5 V dry / ~1.2 V wet. The C3's ADC tops out near 2.5 V, so R1/R2 scale it by 33k/(10k+33k) = 0.767. C1 filters ADC noise. Calibrate dry_v / wet_v at the ESP pin (after the divider).
C2: bulk cap for Wi-Fi current spikes, laid flat.
Mechanical: H1/H2 take the case's locating pins. CASE1 only carries the case 3D model so the 3D viewer shows the board inside the case.
ESP-Soil stake v1.1 github.com/Gunz0Blazin/esp-soil

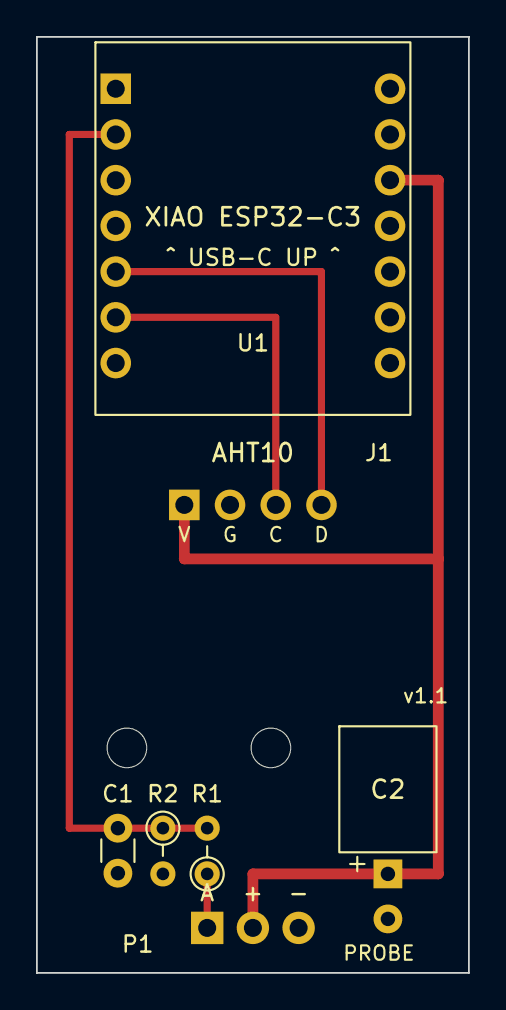
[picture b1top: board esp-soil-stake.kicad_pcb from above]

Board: 2 copper layers, 24.0 x 52.0 mm, 10 parts (0 on the bottom side), 6 nets.
